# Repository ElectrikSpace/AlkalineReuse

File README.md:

# AlkalineReuse
a simple way to reuse alkaline cells

This repository contains schematics, PCB design and software to create a simple alkaline cell charger.

The design is built around a small AVR MCU, the attiny10. Of course, other AVR MCUs can be use without changing the software at all.

Depending on your experiments, you can adjust *charging_time* and *idle_time* of charge cycles.

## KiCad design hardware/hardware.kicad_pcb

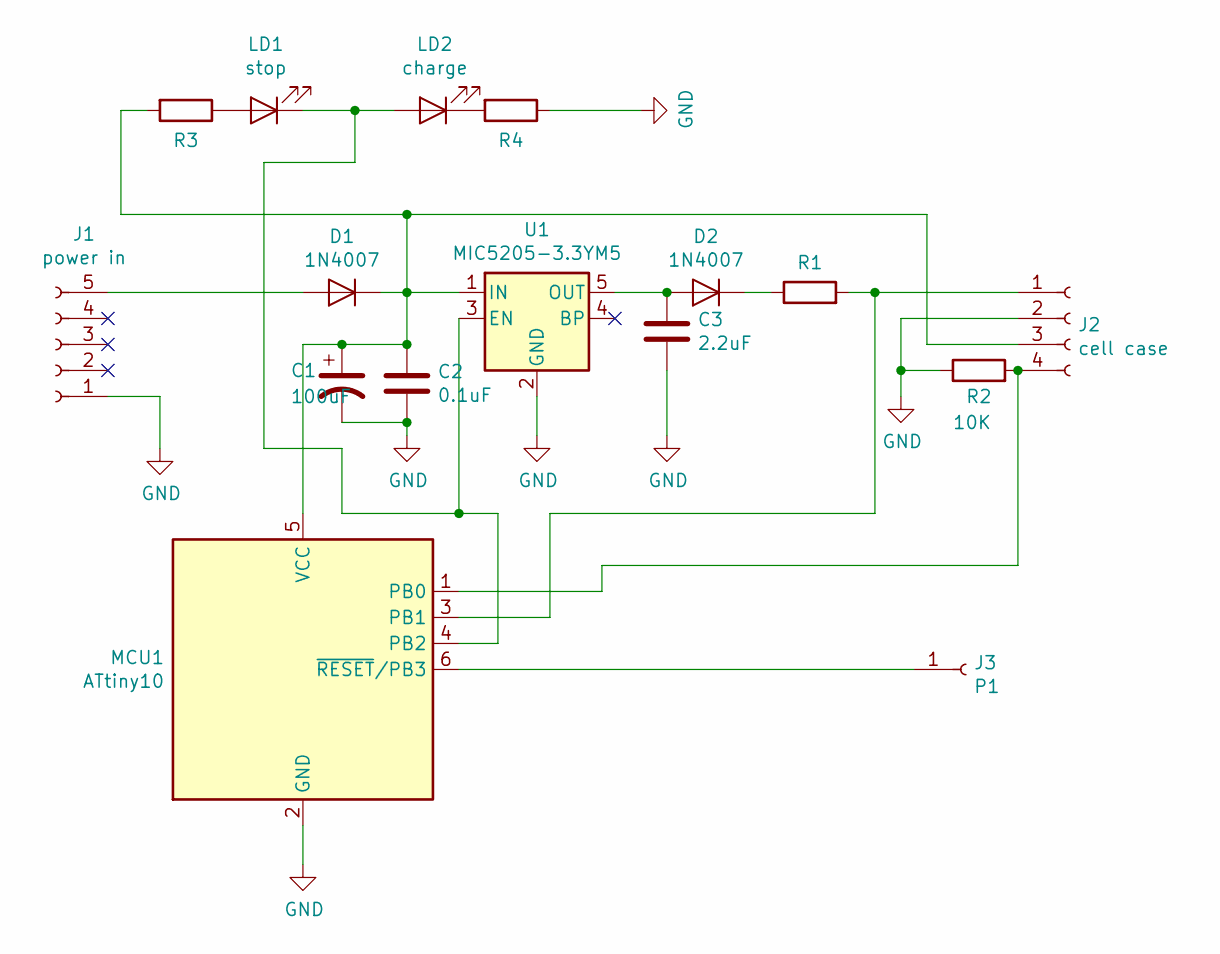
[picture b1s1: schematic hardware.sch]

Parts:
C1: 100uF; CP_Radial_D5.0mm_P2.50mm
C2: 0.1uF; C_1206_3216Metric
C3: 2.2uF; C_1206_3216Metric
D1, D2: 1N4007; D_DO-41_SOD81_P10.16mm_Horizontal
J1: power in; PinHeader_1x05_P2.54mm_Vertical
J2: cell case; PinHeader_1x04_P2.54mm_Vertical
J3: P1; PinHeader_1x01_P2.54mm_Vertical
LD1: stop; LED_D4.0mm
LD2: charge; LED_D4.0mm
MCU1: ATtiny10; SOT-23-6
R1, R3, R4: R; R_0805_2012Metric
R2: 10K; R_1206_3216Metric
U1: MIC5205-3.3YM5; SOT-23-5

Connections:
GND: C1.2, C2.2, C3.2, J1.1, J2.2, MCU1.2 (GND), R2.1, R4.1, U1.2 (GND)
unnamed: C1.1, C2.1, D1.1 (K), J2.3, MCU1.5 (VCC), R3.2, U1.1 (IN)
unnamed: C3.1, D2.2 (A), U1.5 (OUT)
unnamed: D1.2 (A), J1.5
unnamed: D2.1 (K), R1.1
unnamed: J2.1, MCU1.3 (PB1), R1.2
unnamed: J2.4, MCU1.1 (PB0), R2.2
unnamed: J3.1, MCU1.6 (~RESET~/PB3)
unnamed: LD1.1 (K), LD2.2 (A), MCU1.4 (PB2), U1.3 (EN)
unnamed: LD1.2 (A), R3.1
unnamed: LD2.1 (K), R4.2

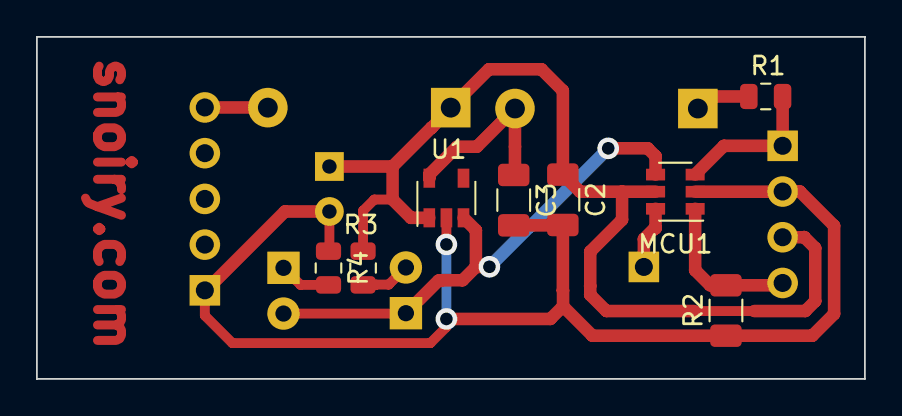
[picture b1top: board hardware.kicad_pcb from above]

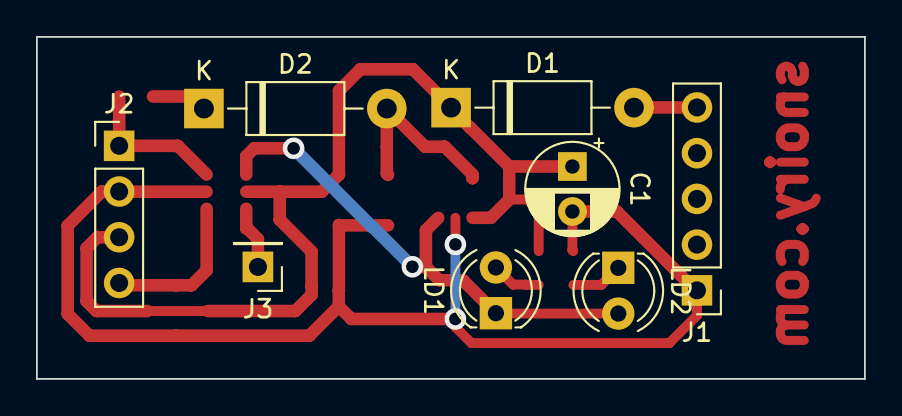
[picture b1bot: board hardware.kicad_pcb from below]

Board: 2 copper layers, 46.0 x 19.0 mm, 16 parts (8 on the bottom side), 11 nets.

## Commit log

2020-04-11 initial commit : v0.1
    - not tested
2020-04-15 update PCB
2020-04-22 add min and max temp and voltage values
2021-02-20 ready to publish
    v1.0
2021-02-20 create readme file
